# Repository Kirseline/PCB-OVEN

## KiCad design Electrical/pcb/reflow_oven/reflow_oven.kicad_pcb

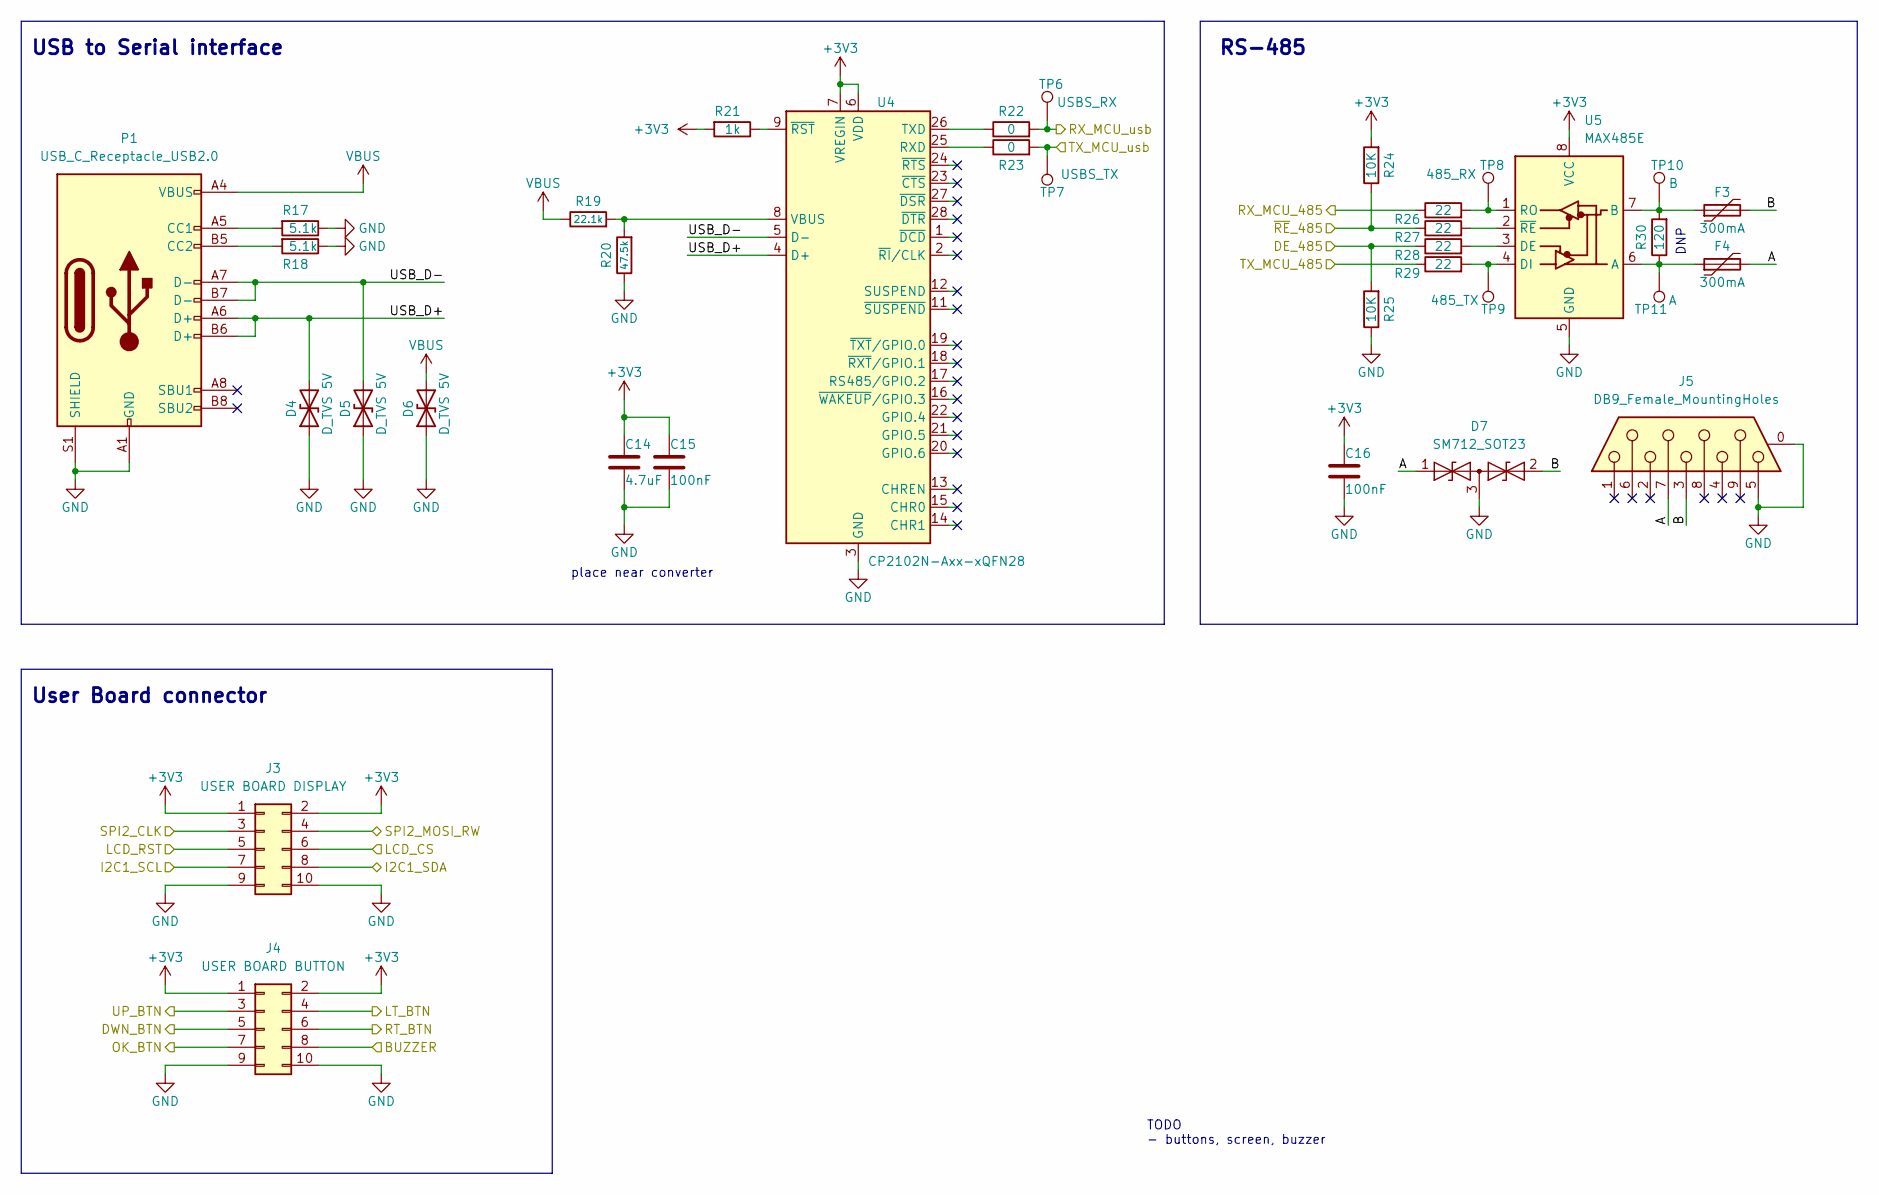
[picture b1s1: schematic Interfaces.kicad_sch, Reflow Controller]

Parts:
C14: 4.7uF; C_0805_2012Metric
C15, C16: 100nF; C_0603_1608Metric
D4, D5, D6: D_TVS 5V; D_SOD-523
D7: SM712_SOT23; SOT-23
F3, F4: 300mA; Fuse_1206_3216Metric_Pad1.42x1.75mm_HandSolder
J3: USER BOARD DISPLAY; SHDR10W66P254_2X5_2019X914X986P
J4: USER BOARD BUTTON; SHDR10W66P254_2X5_2019X914X986P
J5: DB9_Female_MountingHoles; DSUB-9_Female_Horizontal_P2.77x2.84mm_EdgePinOffset7.70mm_H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
P1: USB_C_Receptacle_USB2.0; USB_C_Receptacle_Palconn_UTC16-G
R17, R18: 5.1k; R_0603_1608Metric
R19: 22.1k; R_0603_1608Metric
R20: 47.5k; R_0603_1608Metric
R21: 1k; R_0603_1608Metric
R22, R23: 0; R_0603_1608Metric
R24, R25: 10K; R_0603_1608Metric
R26, R27, R28, R29: 22; R_0603_1608Metric
R30: 120; R_0805_2012Metric_Pad1.20x1.40mm_HandSolder
TP6: USBS_RX; TestPoint_Pad_D1.5mm
TP7: USBS_TX; TestPoint_Pad_D1.5mm
TP8: 485_RX; TestPoint_Pad_D1.5mm
TP9: 485_TX; TestPoint_Pad_D1.5mm
TP10: B; TestPoint_Pad_D1.5mm
TP11: A; TestPoint_Pad_D1.5mm
U4: CP2102N-Axx-xQFN28; QFN-28-1EP_5x5mm_P0.5mm_EP3.35x3.35mm
U5: MAX485E; SOIC127P600X175-8N

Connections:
+3V3: C14.1, C15.1, C16.1, J3.1, J3.2, J4.1, J4.2, R21.2, R24.2, U4.6 (VDD), U4.7 (VREGIN), U5.8 (VCC); also elsewhere on the board
/Interfaces/A: D7.1 (A1), F4.2, J5.7
/Interfaces/B: D7.2 (A2), F3.2, J5.3
/Interfaces/BUZZER: J4.8; also elsewhere on the board
/Interfaces/DE_485: R25.2, R28.1; also elsewhere on the board
/Interfaces/DWN_BTN: J4.5; also elsewhere on the board
/Interfaces/LCD_CS: J3.6; also elsewhere on the board
/Interfaces/LCD_RST: J3.5; also elsewhere on the board
/Interfaces/LT_BTN: J4.4; also elsewhere on the board
/Interfaces/OK_BTN: J4.7; also elsewhere on the board
/Interfaces/RT_BTN: J4.6; also elsewhere on the board
/Interfaces/RX_MCU_485: R26.1; also elsewhere on the board
/Interfaces/RX_MCU_usb: R22.2, TP6.1; also elsewhere on the board
/Interfaces/SPI2_CLK: J3.3; also elsewhere on the board
/Interfaces/SPI2_MOSI_RW: J3.4; also elsewhere on the board
/Interfaces/TX_MCU_485: R29.1; also elsewhere on the board
/Interfaces/TX_MCU_usb: R23.2, TP7.1; also elsewhere on the board
/Interfaces/UP_BTN: J4.3; also elsewhere on the board
/Interfaces/USB_D+: D4.2 (A2), P1.A6 (D+), P1.B6 (D+), U4.4 (D+)
/Interfaces/USB_D-: D5.2 (A2), P1.A7 (D-), P1.B7 (D-), U4.5 (D-)
/Interfaces/~RE_485: R24.1, R27.1; also elsewhere on the board
/MCU_User/I2C1_SCL: J3.7; also elsewhere on the board
/MCU_User/I2C1_SDA: J3.8; also elsewhere on the board
GND: C14.2, C15.2, C16.2, D4.1 (A1), D5.1 (A1), D6.1 (A1), D7.3 (common), J3.9, J3.10, J4.9, J4.10, J5.0 (PAD), J5.5, P1.A1 (GND), P1.A12 (GND), P1.B1 (GND), P1.B12 (GND), P1.S1 (SHIELD), R17.1, R18.1, R20.1, R25.1, U4.3 (GND), U4.29 (GND), U5.5 (GND); also elsewhere on the board
unnamed: F3.1, R30.2, TP10.1, U5.7 (B)
unnamed: F4.1, R30.1, TP11.1, U5.6 (A)
unnamed: P1.A5 (CC1), R17.2
unnamed: P1.B5 (CC2), R18.2
unnamed: R19.2, R20.2, U4.8 (VBUS)
unnamed: R21.1, U4.9 (~RST)
unnamed: R22.1, U4.26 (TXD)
unnamed: R23.1, U4.25 (RXD)
unnamed: R26.2, TP8.1, U5.1 (RO)
unnamed: R27.2, U5.2 (~RE)
unnamed: R28.2, U5.3 (DE)
unnamed: R29.2, TP9.1, U5.4 (DI)
VBUS: D6.2 (A2), P1.A4 (VBUS), P1.A9 (VBUS), P1.B4 (VBUS), P1.B9 (VBUS), R19.1; also elsewhere on the board

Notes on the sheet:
DNP
TODO - buttons, screen, buzzer
User Board connector
RS-485
place near converter
USB to Serial interface

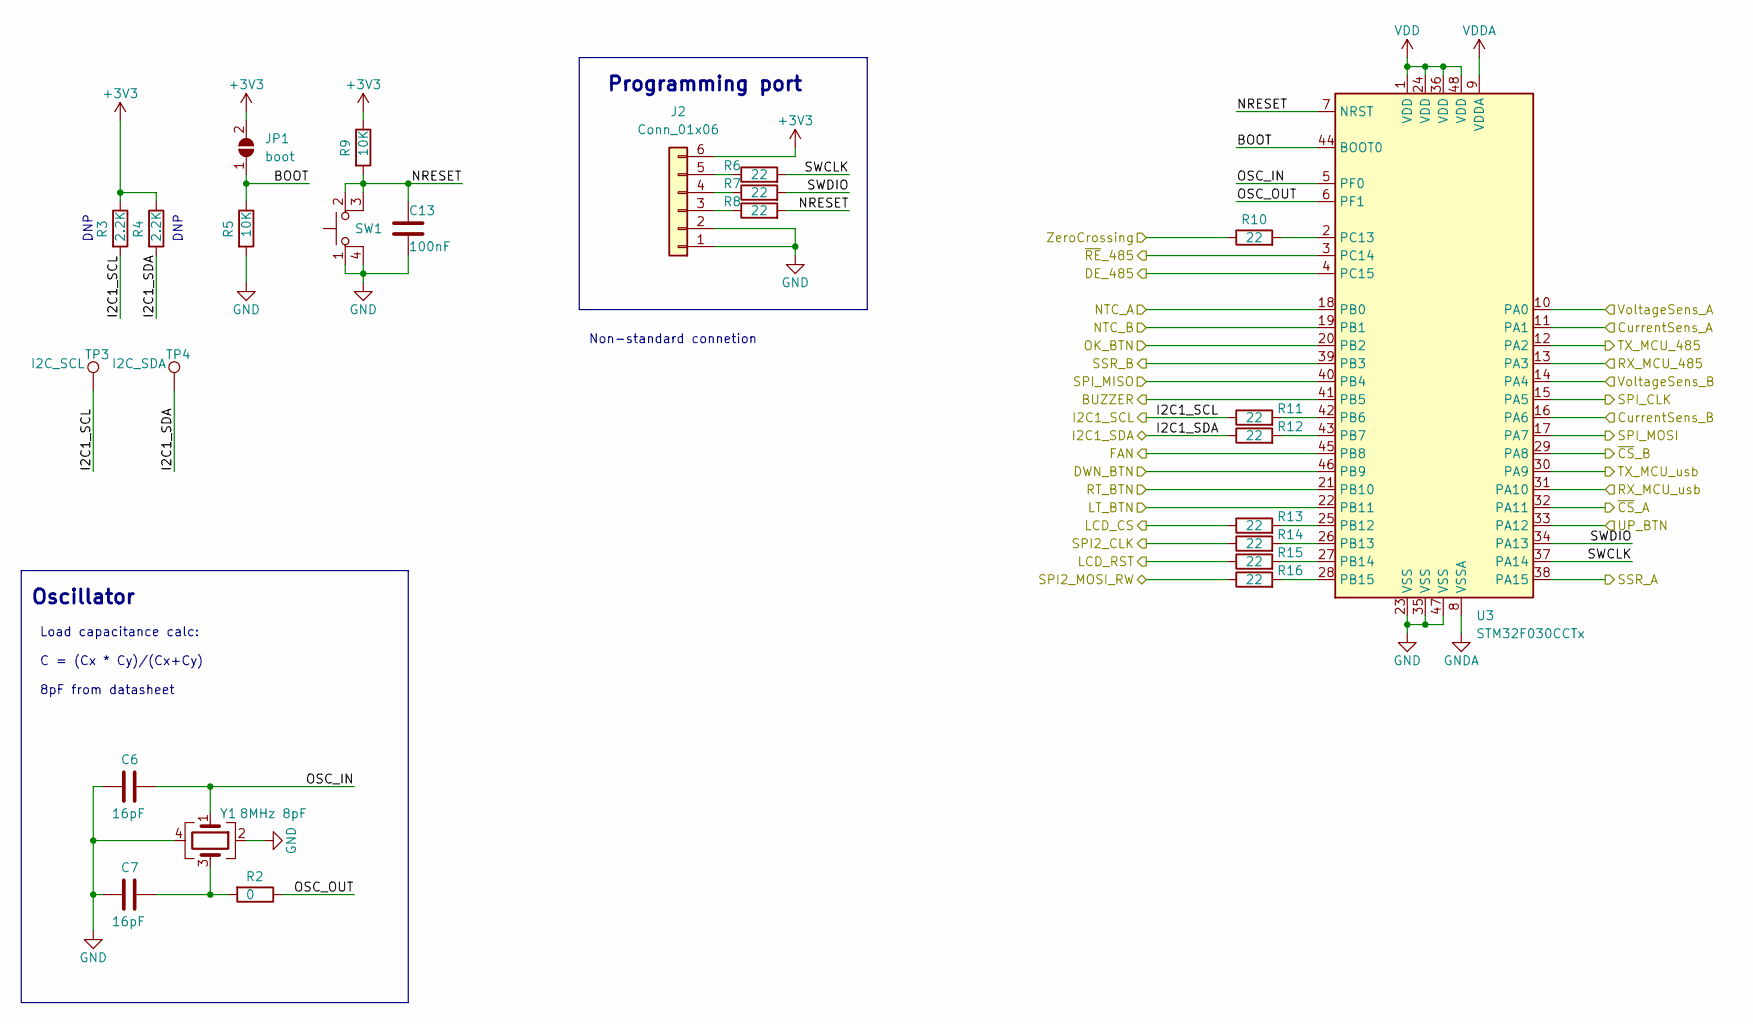
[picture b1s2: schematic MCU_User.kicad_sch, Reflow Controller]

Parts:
C6, C7: 16pF; C_0603_1608Metric
C13: 100nF; C_0603_1608Metric
J2: Conn_01x06; PinHeader_1x06_P2.54mm_Vertical
JP1: boot; SolderJumper-2_P1.3mm_Open_RoundedPad1.0x1.5mm
R2: 0; R_0603_1608Metric
R3, R4: 2.2K; R_0603_1608Metric
R5, R9: 10K; R_0603_1608Metric
R6, R7, R8, R10, R11, R12, R13, R14, R15, R16: 22; R_0603_1608Metric
SW1: SW_MEC_5E; KMR621NGLFS
TP3: I2C_SCL; TestPoint_Pad_D1.5mm
TP4: I2C_SDA; TestPoint_Pad_D1.5mm
U3: STM32F030CCTx; LQFP-48_7x7mm_P0.5mm
Y1: 8MHz 8pF; Crystal_SMD_TXC_7M-4Pin_3.2x2.5mm

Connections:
+3V3: J2.6, JP1.2 (B), R3.1, R4.1, R9.1; also elsewhere on the board
/Actuation/FAN: U3.45 (PB8); also elsewhere on the board
/Actuation/SSR_A: U3.38 (PA15); also elsewhere on the board
/Actuation/SSR_B: U3.39 (PB3); also elsewhere on the board
/Interfaces/BUZZER: U3.41 (PB5); also elsewhere on the board
/Interfaces/DE_485: U3.4 (PC15); also elsewhere on the board
/Interfaces/DWN_BTN: U3.46 (PB9); also elsewhere on the board
/Interfaces/LCD_CS: R13.1; also elsewhere on the board
/Interfaces/LCD_RST: R15.1; also elsewhere on the board
/Interfaces/LT_BTN: U3.22 (PB11); also elsewhere on the board
/Interfaces/OK_BTN: U3.20 (PB2); also elsewhere on the board
/Interfaces/RT_BTN: U3.21 (PB10); also elsewhere on the board
/Interfaces/RX_MCU_485: U3.13 (PA3); also elsewhere on the board
/Interfaces/RX_MCU_usb: U3.31 (PA10); also elsewhere on the board
/Interfaces/SPI2_CLK: R14.1; also elsewhere on the board
/Interfaces/SPI2_MOSI_RW: R16.1; also elsewhere on the board
/Interfaces/TX_MCU_485: U3.12 (PA2); also elsewhere on the board
/Interfaces/TX_MCU_usb: U3.30 (PA9); also elsewhere on the board
/Interfaces/UP_BTN: U3.33 (PA12); also elsewhere on the board
/Interfaces/~RE_485: U3.3 (PC14); also elsewhere on the board
/MCU_User/BOOT: JP1.1 (A), R5.1, U3.44 (BOOT0)
/MCU_User/I2C1_SCL: R3.2, R11.1, TP3.1; also elsewhere on the board
/MCU_User/I2C1_SDA: R4.2, R12.1, TP4.1; also elsewhere on the board
/MCU_User/NRESET: C13.1, R8.2, R9.2, SW1.2, SW1.3 (K), U3.7 (NRST)
/MCU_User/NTC_A: U3.18 (PB0); also elsewhere on the board
/MCU_User/NTC_B: U3.19 (PB1); also elsewhere on the board
/MCU_User/OSC_IN: C6.1, U3.5 (PF0), Y1.1
/MCU_User/OSC_OUT: R2.1, U3.6 (PF1)
/MCU_User/SPI_CLK: U3.15 (PA5); also elsewhere on the board
/MCU_User/SPI_MISO: U3.40 (PB4); also elsewhere on the board
/MCU_User/SPI_MOSI: U3.17 (PA7)
/MCU_User/SWCLK: R6.2, U3.37 (PA14)
/MCU_User/SWDIO: R7.2, U3.34 (PA13)
/MCU_User/ZeroCrossing: R10.1; also elsewhere on the board
/MCU_User/~CS_A: U3.32 (PA11); also elsewhere on the board
/MCU_User/~CS_B: U3.29 (PA8); also elsewhere on the board
/Sensors/Csense_A: U3.11 (PA1); also elsewhere on the board
/Sensors/Csense_B: U3.16 (PA6); also elsewhere on the board
/Sensors/Vsense_A: U3.10 (PA0); also elsewhere on the board
/Sensors/Vsense_B: U3.14 (PA4); also elsewhere on the board
GND: C6.2, C7.2, C13.2, J2.1, J2.2, R5.2, SW1.1, SW1.4, U3.23 (VSS), U3.35 (VSS), U3.47 (VSS), Y1.2, Y1.4; also elsewhere on the board
GNDA: U3.8 (VSSA); also elsewhere on the board
unnamed: C7.1, R2.2, Y1.3
unnamed: J2.3, R8.1
unnamed: J2.4, R7.1
unnamed: J2.5, R6.1
unnamed: R10.2, U3.2 (PC13)
unnamed: R11.2, U3.42 (PB6)
unnamed: R12.2, U3.43 (PB7)
unnamed: R13.2, U3.25 (PB12)
unnamed: R14.2, U3.26 (PB13)
unnamed: R15.2, U3.27 (PB14)
unnamed: R16.2, U3.28 (PB15)
VDD: U3.1 (VDD), U3.24 (VDD), U3.36 (VDD), U3.48 (VDD); also elsewhere on the board
VDDA: U3.9 (VDDA); also elsewhere on the board

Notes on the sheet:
Programming port
Load capacitance calc: C = (Cx * Cy)/(Cx+Cy) 8pF from datasheet
Non-standard connetion
DNP
Oscillator

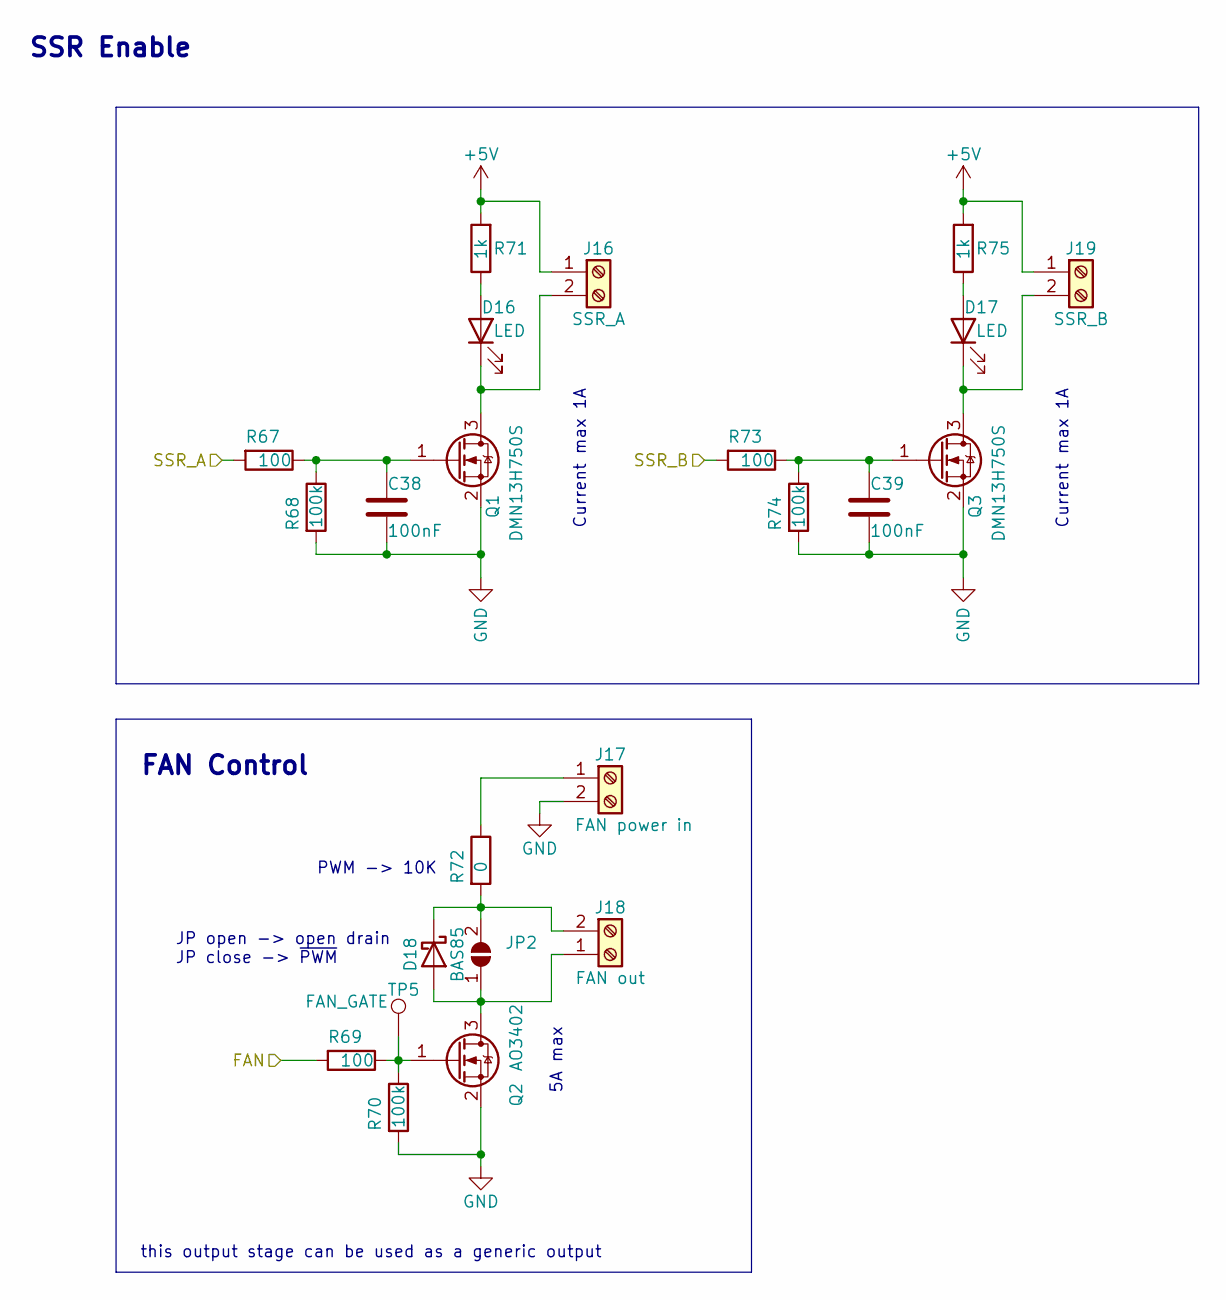
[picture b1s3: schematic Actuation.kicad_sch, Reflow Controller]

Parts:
C38, C39: 100nF; C_0603_1608Metric
D16, D17: LED; LED_0603_1608Metric
D18: BAS85; D_SOD-123F
J16: SSR_A; TerminalBlock_Phoenix_MPT-0,5-2-2.54_1x02_P2.54mm_Horizontal
J17: FAN power in; TerminalBlock_Phoenix_MPT-0,5-2-2.54_1x02_P2.54mm_Horizontal
J18: FAN out; TerminalBlock_Phoenix_MPT-0,5-2-2.54_1x02_P2.54mm_Horizontal
J19: SSR_B; TerminalBlock_Phoenix_MPT-0,5-2-2.54_1x02_P2.54mm_Horizontal
JP2: SolderJumper_2_Open; SolderJumper-2_P1.3mm_Open_RoundedPad1.0x1.5mm
Q1, Q3: DMN13H750S; SOT-23
Q2: AO3402; SOT-23
R67, R69, R73: 100; R_0603_1608Metric
R68, R70, R74: 100k; R_0603_1608Metric
R71, R75: 1k; R_0603_1608Metric
R72: 0; R_0603_1608Metric
TP5: FAN_GATE; TestPoint_Pad_D1.5mm

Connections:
+5V: J16.1, J19.1, R71.2, R75.2; also elsewhere on the board
/Actuation/FAN: R69.2; also elsewhere on the board
/Actuation/SSR_A: R67.2; also elsewhere on the board
/Actuation/SSR_B: R73.2; also elsewhere on the board
GND: C38.2, C39.2, J17.2, Q1.2 (S), Q2.2 (S), Q3.2 (S), R68.2, R70.2, R74.2; also elsewhere on the board
unnamed: C38.1, Q1.1 (G), R67.1, R68.1
unnamed: C39.1, Q3.1 (G), R73.1, R74.1
unnamed: D16.1 (K), J16.2, Q1.3 (D)
unnamed: D16.2 (A), R71.1
unnamed: D17.1 (K), J19.2, Q3.3 (D)
unnamed: D17.2 (A), R75.1
unnamed: D18.1 (K), J18.2, JP2.2 (B), R72.2
unnamed: D18.2 (A), J18.1, JP2.1 (A), Q2.3 (D)
unnamed: J17.1, R72.1
unnamed: Q2.1 (G), R69.1, R70.1, TP5.1

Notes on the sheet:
PWM -> 10K
Current max 1A
FAN Control
5A max
SSR Enable
this output stage can be used as a generic output
JP open -> open drain JP close -> ~{PWM}

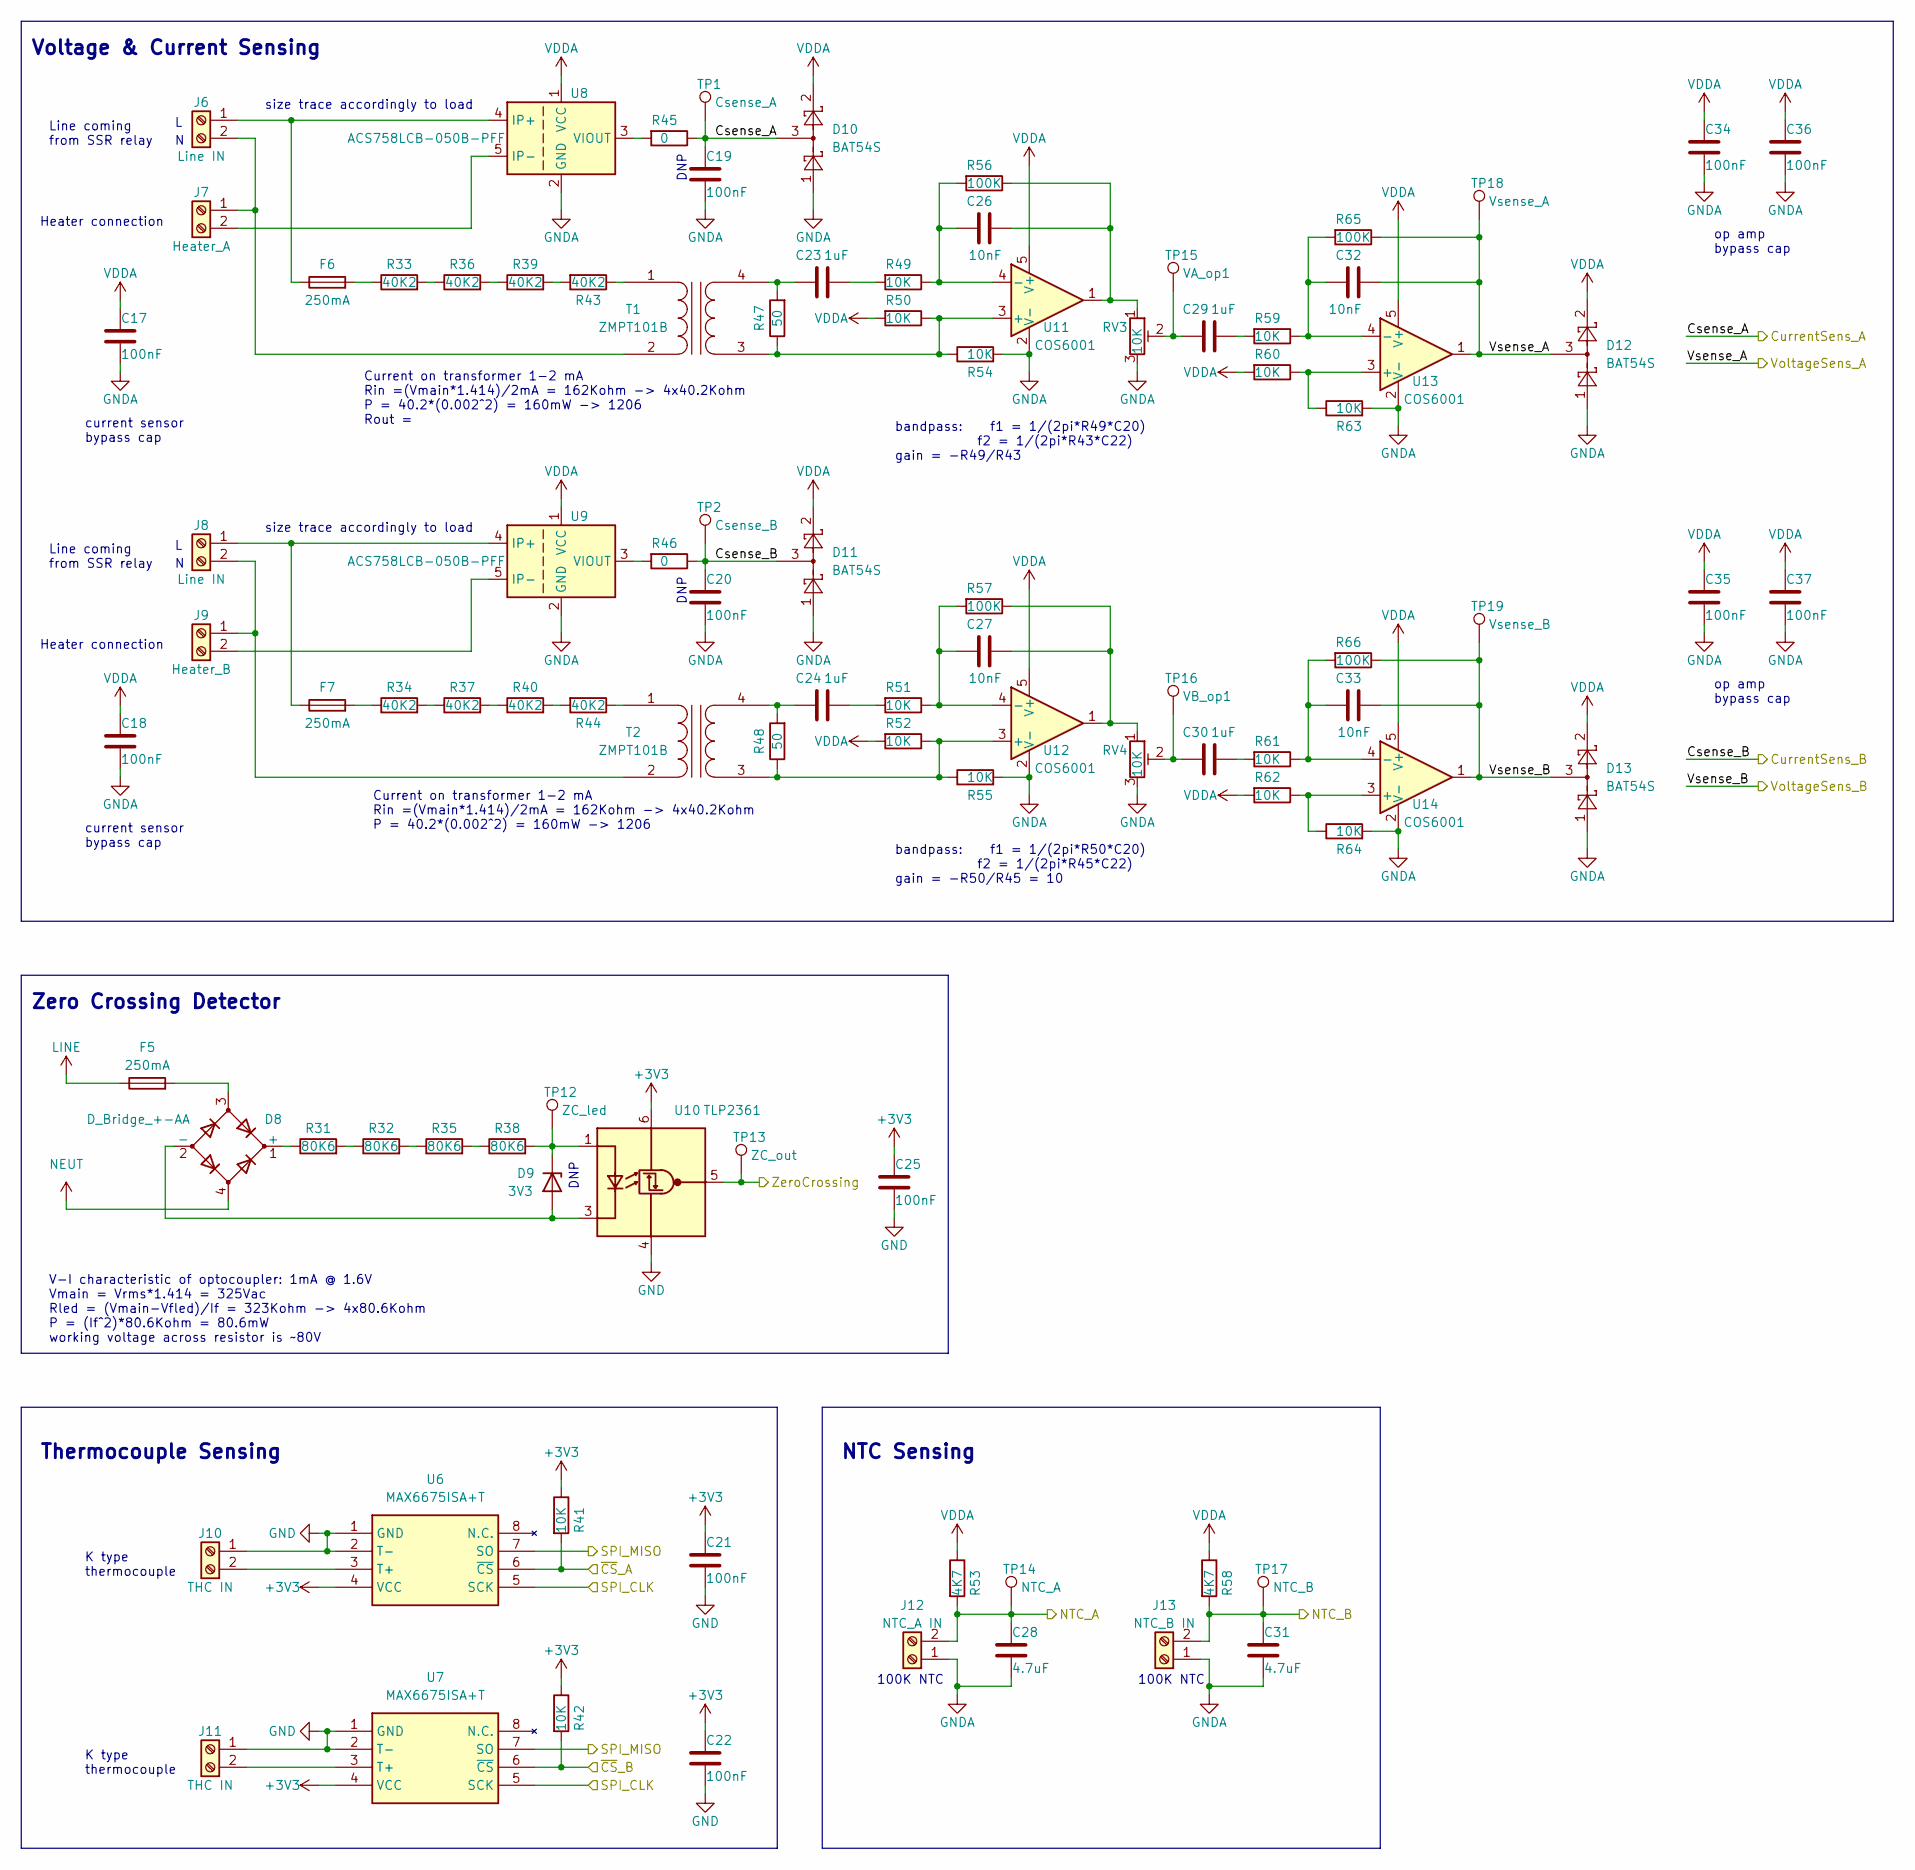
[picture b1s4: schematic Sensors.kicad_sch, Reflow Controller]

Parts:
C17, C18, C19, C20, C21, C22, C25, C34, C35, C36, C37: 100nF; C_0603_1608Metric
C23, C24, C29, C30: 1uF; C_0805_2012Metric
C26, C27, C32, C33: 10nF; C_0603_1608Metric
C28, C31: 4.7uF; C_0805_2012Metric
D8: D_Bridge_+-AA; DIP825W58P510L832H472Q4N
D9: 3V3; D_SOD-123
D10, D11, D12, D13: BAT54S; SOT-23
F5, F6, F7: 250mA; Circular_fuse
J6, J8: Line IN; TerminalBlock_bornier-2_P5.08mm
J7: Heater_A; TerminalBlock_bornier-2_P5.08mm
J9: Heater_B; TerminalBlock_bornier-2_P5.08mm
J10, J11: THC IN; TerminalBlock_Phoenix_MPT-0,5-2-2.54_1x02_P2.54mm_Horizontal
J12: NTC_A IN; TerminalBlock_Phoenix_MPT-0,5-2-2.54_1x02_P2.54mm_Horizontal
J13: NTC_B IN; TerminalBlock_Phoenix_MPT-0,5-2-2.54_1x02_P2.54mm_Horizontal
R31, R32, R35, R38: 80K6; R_0805_2012Metric_Pad1.20x1.40mm_HandSolder
R33, R34, R36, R37, R39, R40, R43, R44: 40K2; R_1206_3216Metric_Pad1.30x1.75mm_HandSolder
R41, R42, R49, R50, R51, R52, R54, R55, R59, R60, R61, R62, R63, R64: 10K; R_0603_1608Metric
R45, R46: 0; R_0603_1608Metric
R47, R48: 50; R_0805_2012Metric_Pad1.20x1.40mm_HandSolder
R53, R58: 4K7; R_0603_1608Metric
R56, R57, R65, R66: 100K; R_0603_1608Metric
RV3, RV4: 10K; TC33X2503E
T1, T2: ZMPT101B
TP1: Csense_A; TestPoint_Pad_D1.5mm
TP2: Csense_B; TestPoint_Pad_D1.5mm
TP12: ZC_led; TestPoint_Pad_D1.5mm
TP13: ZC_out; TestPoint_Pad_D1.5mm
TP14: NTC_A; TestPoint_Pad_D1.5mm
TP15: VA_op1; TestPoint_Pad_D1.5mm
TP16: VB_op1; TestPoint_Pad_D1.5mm
TP17: NTC_B; TestPoint_Pad_D1.5mm
TP18: Vsense_A; TestPoint_Pad_D1.5mm
TP19: Vsense_B; TestPoint_Pad_D1.5mm
U6, U7: MAX6675ISA+T; SOIC127P600X175-8N; Mouser Part Number 700-MAX6675ISAT
U8, U9: ACS758LCB-050B-PFF; Allegro_CB_PFF
U10: TLP2361; 11-4L1S_5-PIN-SOIC_
U11, U12, U13, U14: COS6001; SOT-23-5

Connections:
+3V3: C21.1, C22.1, C25.1, R41.1, R42.1, U6.4 (VCC), U7.4 (VCC), U10.6 (VDD); also elsewhere on the board
/MCU_User/NTC_A: C28.1, J12.2, R53.2, TP14.1; also elsewhere on the board
/MCU_User/NTC_B: C31.1, J13.2, R58.2, TP17.1; also elsewhere on the board
/MCU_User/SPI_CLK: U6.5 (SCK), U7.5 (SCK); also elsewhere on the board
/MCU_User/SPI_MISO: U6.7 (SO), U7.7 (SO); also elsewhere on the board
/MCU_User/ZeroCrossing: TP13.1, U10.5 (VO); also elsewhere on the board
/MCU_User/~CS_A: R41.2, U6.6 (~CS); also elsewhere on the board
/MCU_User/~CS_B: R42.2, U7.6 (~CS); also elsewhere on the board
/Sensors/Csense_A: C19.1, D10.3, R45.1, TP1.1; also elsewhere on the board
/Sensors/Csense_B: C20.1, D11.3, R46.1, TP2.1; also elsewhere on the board
/Sensors/Vsense_A: C32.2, D12.3, R65.1, TP18.1, U13.1; also elsewhere on the board
/Sensors/Vsense_B: C33.2, D13.3, R66.1, TP19.1, U14.1; also elsewhere on the board
GND: C21.2, C22.2, C25.2, J10.1, J11.1, U6.1 (GND), U6.2 (T-), U7.1 (GND), U7.2 (T-), U10.4 (GND); also elsewhere on the board
GNDA: C17.2, C18.2, C19.2, C20.2, C28.2, C31.2, C34.2, C35.2, C36.2, C37.2, D10.1, D11.1, D12.1, D13.1, J12.1, J13.1, R54.2, R55.2, R63.2, R64.2, RV3.3, RV4.3, U8.2 (GND), U9.2 (GND), U11.2 (V-), U12.2 (V-), U13.2 (V-), U14.2 (V-); also elsewhere on the board
LINE: F5.1; also elsewhere on the board
NEUT: D8.4; also elsewhere on the board
unnamed: C23.1, R47.2, T1.4 (SB)
unnamed: C23.2, R49.2
unnamed: C24.1, R48.2, T2.4 (SB)
unnamed: C24.2, R51.2
unnamed: C26.1, R49.1, R56.2, U11.4 (-)
unnamed: C26.2, R56.1, RV3.1, U11.1
unnamed: C27.1, R51.1, R57.2, U12.4 (-)
unnamed: C27.2, R57.1, RV4.1, U12.1
unnamed: C29.1, RV3.2, TP15.1
unnamed: C29.2, R59.2
unnamed: C30.1, RV4.2, TP16.1
unnamed: C30.2, R61.2
unnamed: C32.1, R59.1, R65.2, U13.4 (-)
unnamed: C33.1, R61.1, R66.2, U14.4 (-)
unnamed: D8.1 (+), R31.1
unnamed: D8.2 (-), D9.2 (A), U10.3 (K)
unnamed: D8.3, F5.2
unnamed: D9.1 (K), R38.2, TP12.1, U10.1 (A)
unnamed: F6.1, J6.1 (Pin_2), U8.4 (IP+)
unnamed: F6.2, R33.1
unnamed: F7.1, J8.1, U9.4 (IP+)
unnamed: F7.2, R34.1
unnamed: J6.2 (Pin_1), J7.1 (Pin_2), T1.2 (AB)
unnamed: J7.2 (Pin_1), U8.5 (IP-)
unnamed: J8.2, J9.1, T2.2 (AB)
unnamed: J9.2, U9.5 (IP-)
unnamed: J10.2, U6.3 (T+)
unnamed: J11.2, U7.3 (T+)
unnamed: R31.2, R32.1
unnamed: R32.2, R35.1
unnamed: R33.2, R36.1
unnamed: R34.2, R37.1
unnamed: R35.2, R38.1
unnamed: R36.2, R39.1
unnamed: R37.2, R40.1
unnamed: R39.2, R43.2
unnamed: R40.2, R44.2
unnamed: R43.1, T1.1 (AA)
unnamed: R44.1, T2.1 (AA)
unnamed: R45.2, U8.3 (VIOUT)
unnamed: R46.2, U9.3 (VIOUT)
unnamed: R47.1, R50.1, R54.1, T1.3 (SA), U11.3 (+)
unnamed: R48.1, R52.1, R55.1, T2.3 (SA), U12.3 (+)
unnamed: R60.1, R63.1, U13.3 (+)
unnamed: R62.1, R64.1, U14.3 (+)
VDDA: C17.1, C18.1, C34.1, C35.1, C36.1, C37.1, D10.2, D11.2, D12.2, D13.2, R50.2, R52.2, R53.1, R58.1, R60.2, R62.2, U8.1 (VCC), U9.1 (VCC), U11.5 (V+), U12.5 (V+), U13.5 (V+), U14.5 (V+); also elsewhere on the board

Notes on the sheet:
V-I characteristic of optocoupler: 1mA @ 1.6V Vmain = Vrms*1.414 = 325Vac Rled = (Vmain-Vfled)/If = 323Kohm -> 4x80.6Kohm P = (If^2)*80.6Kohm = 80.6mW working voltage across resistor is ~80V
Line coming from SSR relay
Voltage & Current Sensing
100K NTC
size trace accordingly to load
Current on transformer 1-2 mA Rin =(Vmain*1.414)/2mA = 162Kohm -> 4x40.2Kohm P = 40.2*(0.002^2) = 160mW -> 1206 Rout =
Current on transformer 1-2 mA Rin =(Vmain*1.414)/2mA = 162Kohm -> 4x40.2Kohm P = 40.2*(0.002^2) = 160mW -> 1206
bandpass: f1 = 1/(2pi*R50*C20) f2 = 1/(2pi*R45*C22) gain = -R50/R45 = 10
Heater connection
DNP
op amp bypass cap
NTC Sensing
K type thermocouple
bandpass: f1 = 1/(2pi*R49*C20) f2 = 1/(2pi*R43*C22) gain = -R49/R43
Zero Crossing Detector
DNP
current sensor bypass cap
Thermocouple Sensing

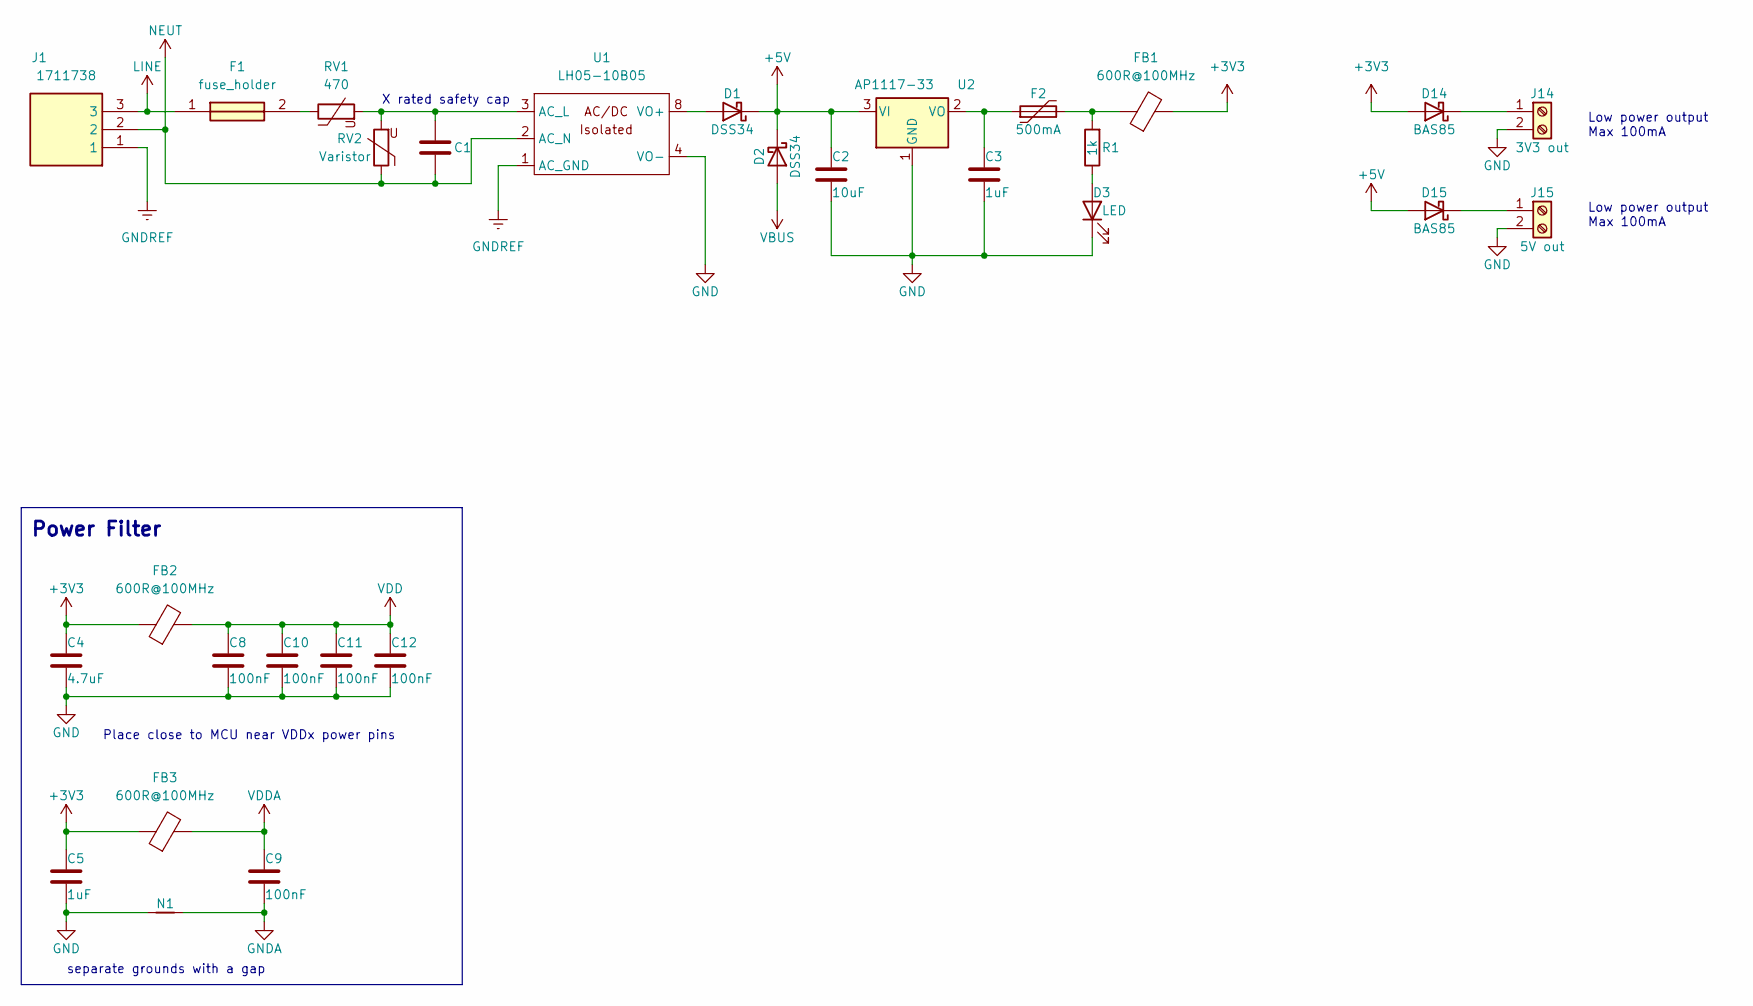
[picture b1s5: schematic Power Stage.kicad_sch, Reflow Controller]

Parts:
C1: C; MXH104K305E10
C2: 10uF; C_0805_2012Metric
C3, C5: 1uF; C_0805_2012Metric
C4: 4.7uF; C_0805_2012Metric
C8, C9, C10, C11, C12: 100nF; C_0603_1608Metric
D1, D2: DSS34; D_SOD-123F
D3: LED; LED_0603_1608Metric
D14, D15: BAS85; D_SOD-123F
F1: fuse_holder; 64600001223; Mouser Part Number 576-64600001223
F2: 500mA; Fuse_1206_3216Metric_Pad1.42x1.75mm_HandSolder
FB1, FB2, FB3: 600R@100MHz; R_0603_1608Metric_Pad0.98x0.95mm_HandSolder
J1: 1711738; Mouser Part Number 651-1711738
J14: 3V3 out; TerminalBlock_Phoenix_MPT-0,5-2-2.54_1x02_P2.54mm_Horizontal
J15: 5V out; TerminalBlock_Phoenix_MPT-0,5-2-2.54_1x02_P2.54mm_Horizontal
N1: Net-Tie_2; NetTie-2_SMD_Pad2.0mm
R1: 1k; R_0603_1608Metric
RV1: 470; MOV_20D241k
RV2: Varistor; MOV_20D241k
U1: LH05-10B05; LH05-13B05
U2: AP1117-33; SOT-223-3_TabPin2

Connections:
+3V3: C4.1, C5.1, D14.2 (A), FB1.2, FB2.1, FB3.1; also elsewhere on the board
+5V: C2.1, D1.1 (K), D2.1 (K), D15.2 (A), U2.3 (VI); also elsewhere on the board
GND: C2.2, C3.2, C4.2, C5.2, C8.2, C10.2, C11.2, C12.2, D3.1 (K), J14.2, J15.2, N1.1, U1.4 (VO-), U2.1 (GND); also elsewhere on the board
GNDA: C9.2, N1.2; also elsewhere on the board
GNDREF: J1.1, U1.1 (AC_GND)
LINE: F1.1, J1.3; also elsewhere on the board
NEUT: C1.2, J1.2, RV2.1, U1.2 (AC_N); also elsewhere on the board
unnamed: C1.1, RV1.2, RV2.2, U1.3 (AC_L)
unnamed: C3.1, F2.1, U2.2 (VO)
unnamed: D1.2 (A), U1.8 (VO+)
unnamed: D3.2 (A), R1.1
unnamed: D14.1 (K), J14.1
unnamed: D15.1 (K), J15.1
unnamed: F1.2, RV1.1
unnamed: F2.2, FB1.1, R1.2
VBUS: D2.2 (A); also elsewhere on the board
VDD: C8.1, C10.1, C11.1, C12.1, FB2.2; also elsewhere on the board
VDDA: C9.1, FB3.2; also elsewhere on the board

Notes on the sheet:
Place close to MCU near VDDx power pins
Low power output Max 100mA
X rated safety cap
Power Filter
separate grounds with a gap

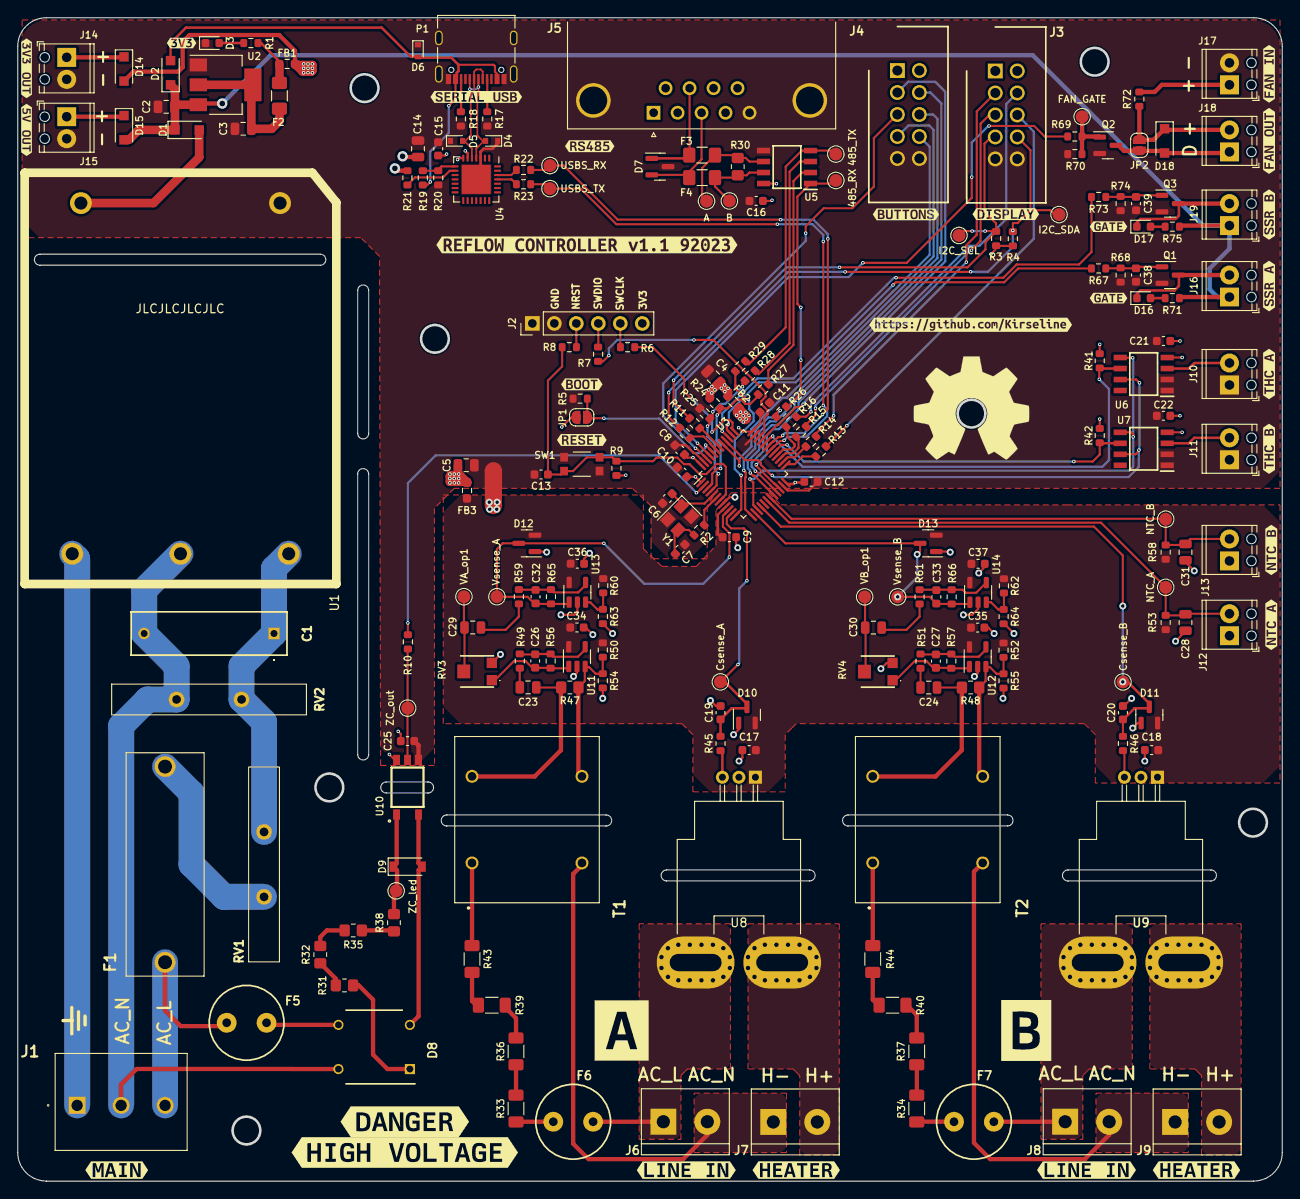
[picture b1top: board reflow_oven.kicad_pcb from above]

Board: 2 copper layers, 145.9 x 134.2 mm, 239 parts (0 on the bottom side), 138 nets.

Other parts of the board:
kibuzzard-64E4F8B7: G***; kibuzzard-64E4F8B7
kibuzzard-64E4F9A0, kibuzzard-64E4F9A0#2: G***; kibuzzard-64E4F9A0
kibuzzard-64E4F9DC: G***; kibuzzard-64E4F9DC
kibuzzard-64E4F49B: G***; kibuzzard-64E4F49B
kibuzzard-64E4F476: G***; kibuzzard-64E4F476
kibuzzard-64E4F882: G***; kibuzzard-64E4F882
kibuzzard-64E4F997, kibuzzard-64E4F997#2: G***; kibuzzard-64E4F997
kibuzzard-64E4FDFA: G***; kibuzzard-64E4FDFA
kibuzzard-64E4FE01: G***; kibuzzard-64E4FE01
kibuzzard-64E5CE1E: G***; kibuzzard-64E5CE1E
kibuzzard-64E5CE2C: G***; kibuzzard-64E5CE2C
kibuzzard-64E5FA1C, kibuzzard-64E5FA1C#2: G***; kibuzzard-64E5FA1C
kibuzzard-64E5FC4C: G***; kibuzzard-64E5FC4C
kibuzzard-64E5FC57: G***; kibuzzard-64E5FC57
kibuzzard-64E5FCEC: G***; kibuzzard-64E5FCEC
kibuzzard-64E50E47: G***; kibuzzard-64E50E47
kibuzzard-64E62C67: G***; kibuzzard-64E62C67
kibuzzard-64E602C4: G***; kibuzzard-64E602C4
kibuzzard-64E607E3: G***; kibuzzard-64E607E3
kibuzzard-64E610EC: G***; kibuzzard-64E610EC
kibuzzard-64E624F7: G***; kibuzzard-64E624F7
kibuzzard-64E625F5: G***; kibuzzard-64E625F5
kibuzzard-64E5011B: G***; kibuzzard-64E5011B
kibuzzard-64E6252A: G***; kibuzzard-64E6252A
kibuzzard-64E50110: G***; kibuzzard-64E50110
kibuzzard-64E50301: G***; kibuzzard-64E50301
kibuzzard-64E62979: G***; kibuzzard-64E62979
